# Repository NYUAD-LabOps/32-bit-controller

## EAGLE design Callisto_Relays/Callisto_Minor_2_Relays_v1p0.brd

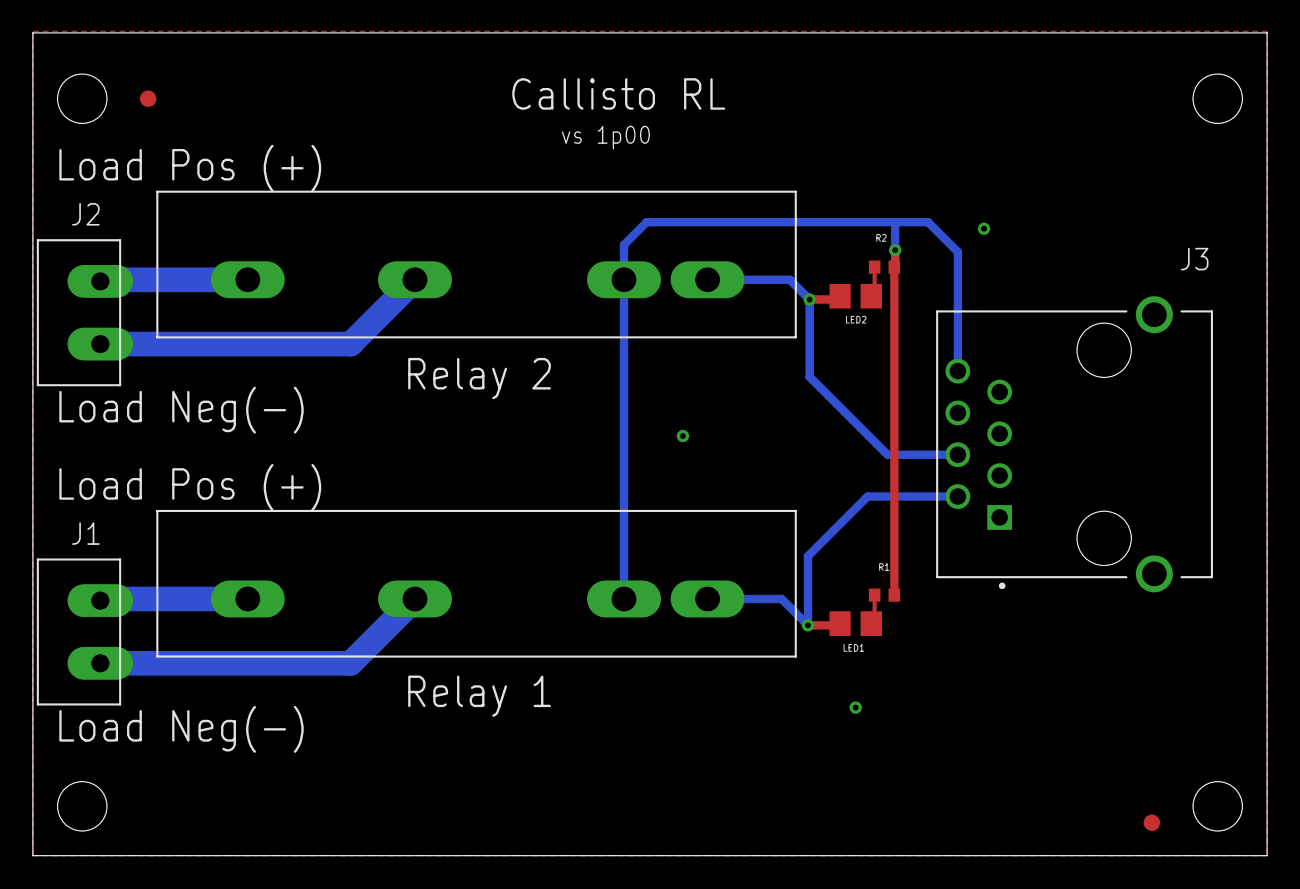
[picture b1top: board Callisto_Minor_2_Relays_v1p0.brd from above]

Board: 2 copper layers, 75.0 x 50.0 mm, 11 parts (0 on the bottom side), 10 nets.

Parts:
J1, J2: 2-pos; 2_3.81MM_PITCH
J3: RJ45_TH_VERT; ASSMANN_A-2014-2S-4-N-R
LED1, LED2: Green; 0805
R1, R2: 470R0; 0402
U$1, U$2: FIDUCIAL_1MM
U$3, U$5: RELAY_KYOTO_KF0604D

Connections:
GND: J3.1, J3.6
unnamed: LED1.1, R1.P$1
unnamed: LED2.1, R2.P$1
RELAY_1: J3.2, LED1.2, U$3.P$1
RELAY_2: J3.4, LED2.2, U$5.P$1
RO_NEG_1: J1.P$2, U$3.P$3
RO_NEG_2: J2.P$2, U$5.P$3
RO_POS_1: J1.P$1, U$3.P$4
RO_POS_2: J2.P$1, U$5.P$4
VDD5: J3.8, R1.P$2, R2.P$2, U$3.P$2, U$5.P$2

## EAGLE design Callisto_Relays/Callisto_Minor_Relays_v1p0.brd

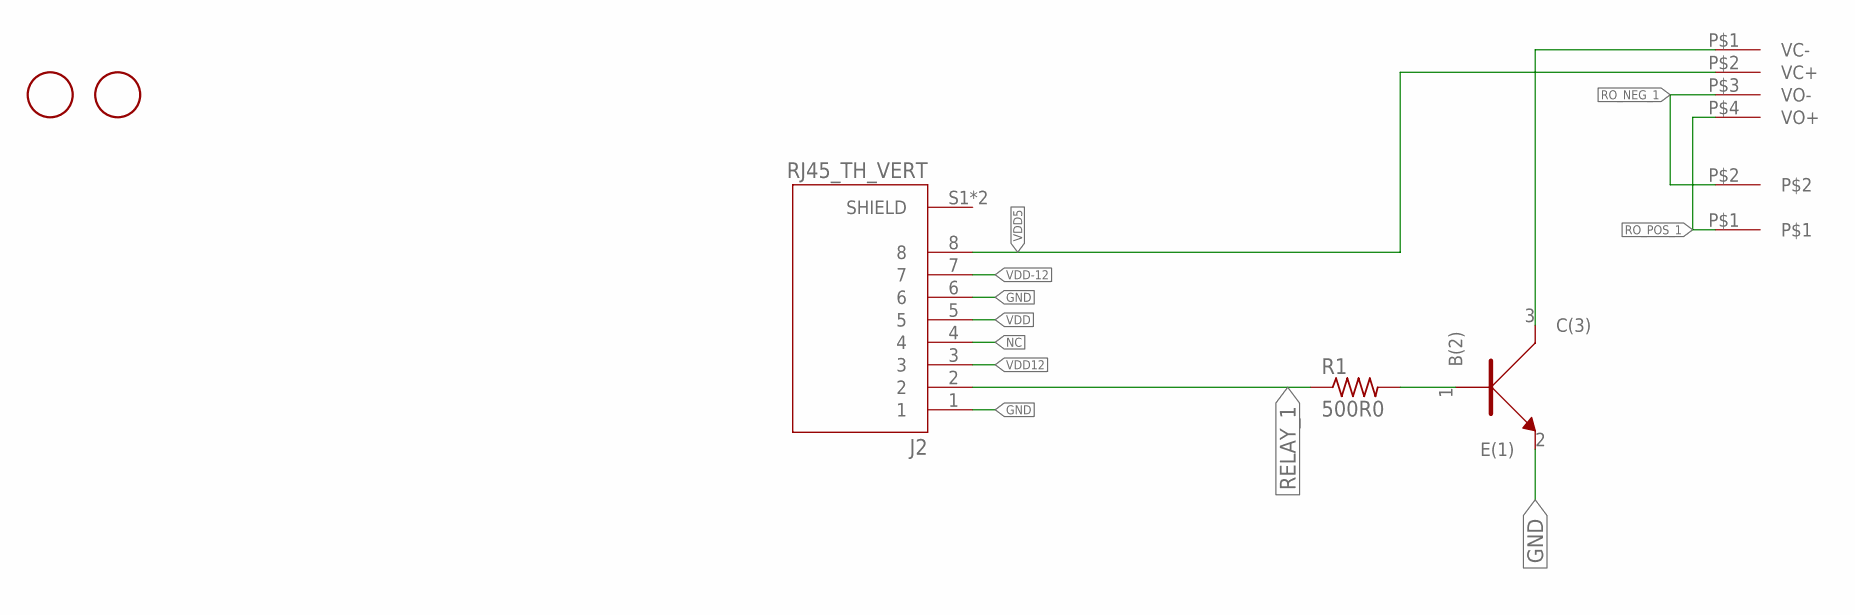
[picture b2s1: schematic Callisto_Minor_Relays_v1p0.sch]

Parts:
J1: 2-pos; 2_3.81MM_PITCH
J2: RJ45_TH_VERT; ASSMANN_A-2014-2S-4-N-R
R1: 500R0; 0402
U2: NPN; SOT323
U$1, U$2: FIDUCIAL_1MM
U$3: RELAY_KYOTO_KF0604D

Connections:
GND: J2.1, J2.6, U2.2 (E(1))
unnamed: R1.P$2 (2), U2.1 (B(2))
unnamed: U2.3 (C(3)), U$3.P$1 (VC-)
NC: J2.4
RELAY_1: J2.2, R1.P$1 (1)
RO_NEG_1: J1.P$2, U$3.P$3 (VO-)
RO_POS_1: J1.P$1, U$3.P$4 (VO+)
VDD: J2.5
VDD5: J2.8, U$3.P$2 (VC+)
VDD12: J2.3
VDD-12: J2.7

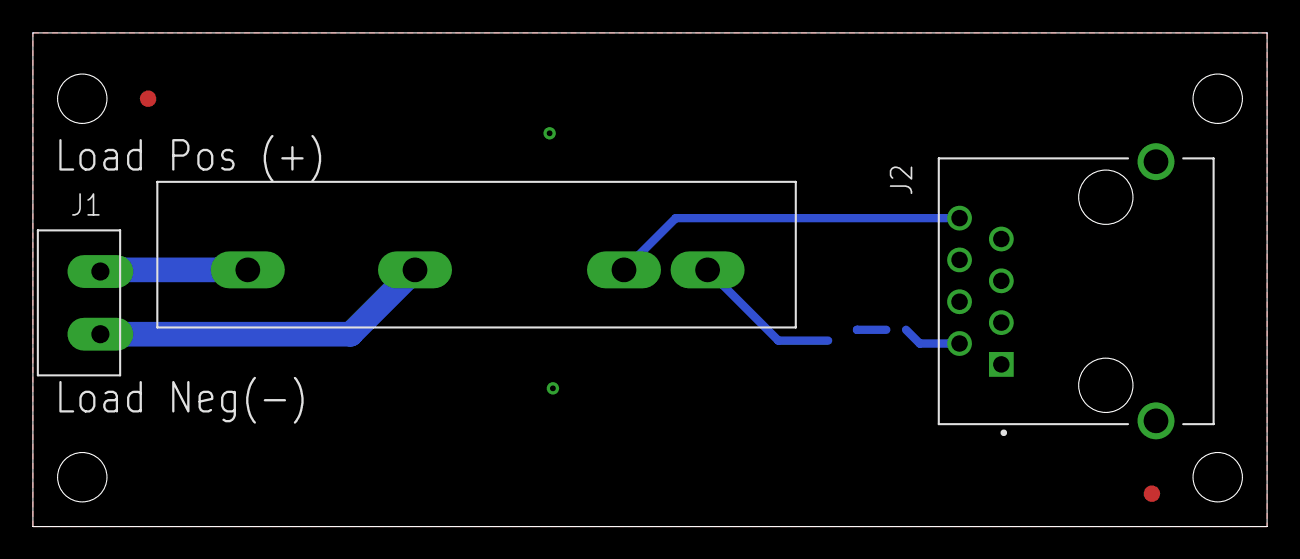
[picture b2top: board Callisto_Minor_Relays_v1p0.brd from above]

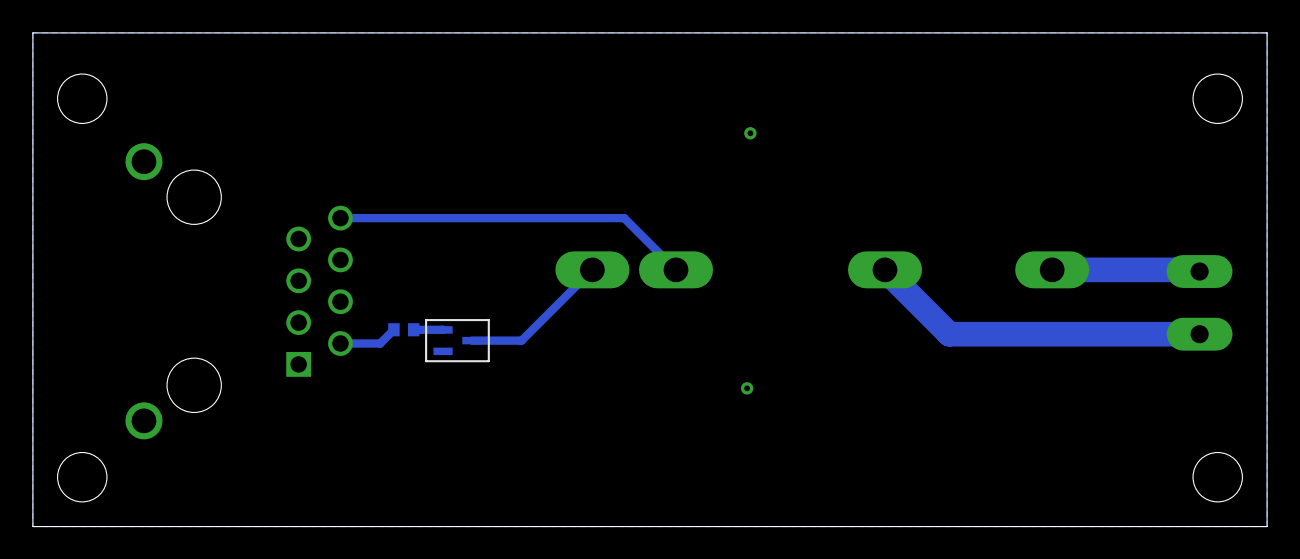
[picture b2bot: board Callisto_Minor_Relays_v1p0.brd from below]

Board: 2 copper layers, 75.0 x 30.0 mm, 7 parts (2 on the bottom side), 7 nets.

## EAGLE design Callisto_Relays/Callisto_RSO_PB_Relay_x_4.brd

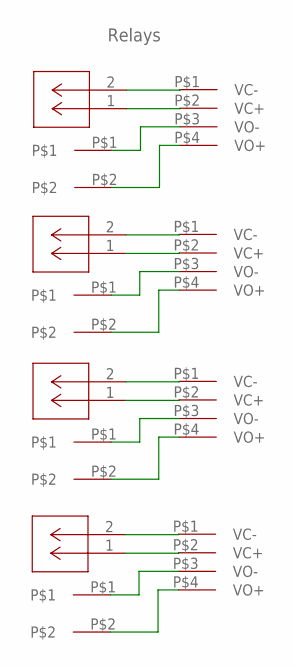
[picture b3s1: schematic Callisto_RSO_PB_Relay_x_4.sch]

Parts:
J4, J6, J8, J10: CONN_530470210_PICOBLADE_X_2; CON_530470210_MOL
J5, J7, J9, J11: 2-pos; 2_3.81MM_PITCH
U$1, U$2, U$3, U$4: RELAY_KYOTO_KF0604D

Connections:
unnamed: J4.1, U$1.P$2 (VC+)
unnamed: J4.2, U$1.P$1 (VC-)
unnamed: J5.P$1, U$1.P$3 (VO-)
unnamed: J5.P$2, U$1.P$4 (VO+)
unnamed: J6.1, U$2.P$2 (VC+)
unnamed: J6.2, U$2.P$1 (VC-)
unnamed: J7.P$1, U$2.P$3 (VO-)
unnamed: J7.P$2, U$2.P$4 (VO+)
unnamed: J8.1, U$3.P$2 (VC+)
unnamed: J8.2, U$3.P$1 (VC-)
unnamed: J9.P$1, U$3.P$3 (VO-)
unnamed: J9.P$2, U$3.P$4 (VO+)
unnamed: J10.1, U$4.P$2 (VC+)
unnamed: J10.2, U$4.P$1 (VC-)
unnamed: J11.P$1, U$4.P$3 (VO-)
unnamed: J11.P$2, U$4.P$4 (VO+)

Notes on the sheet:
Relays

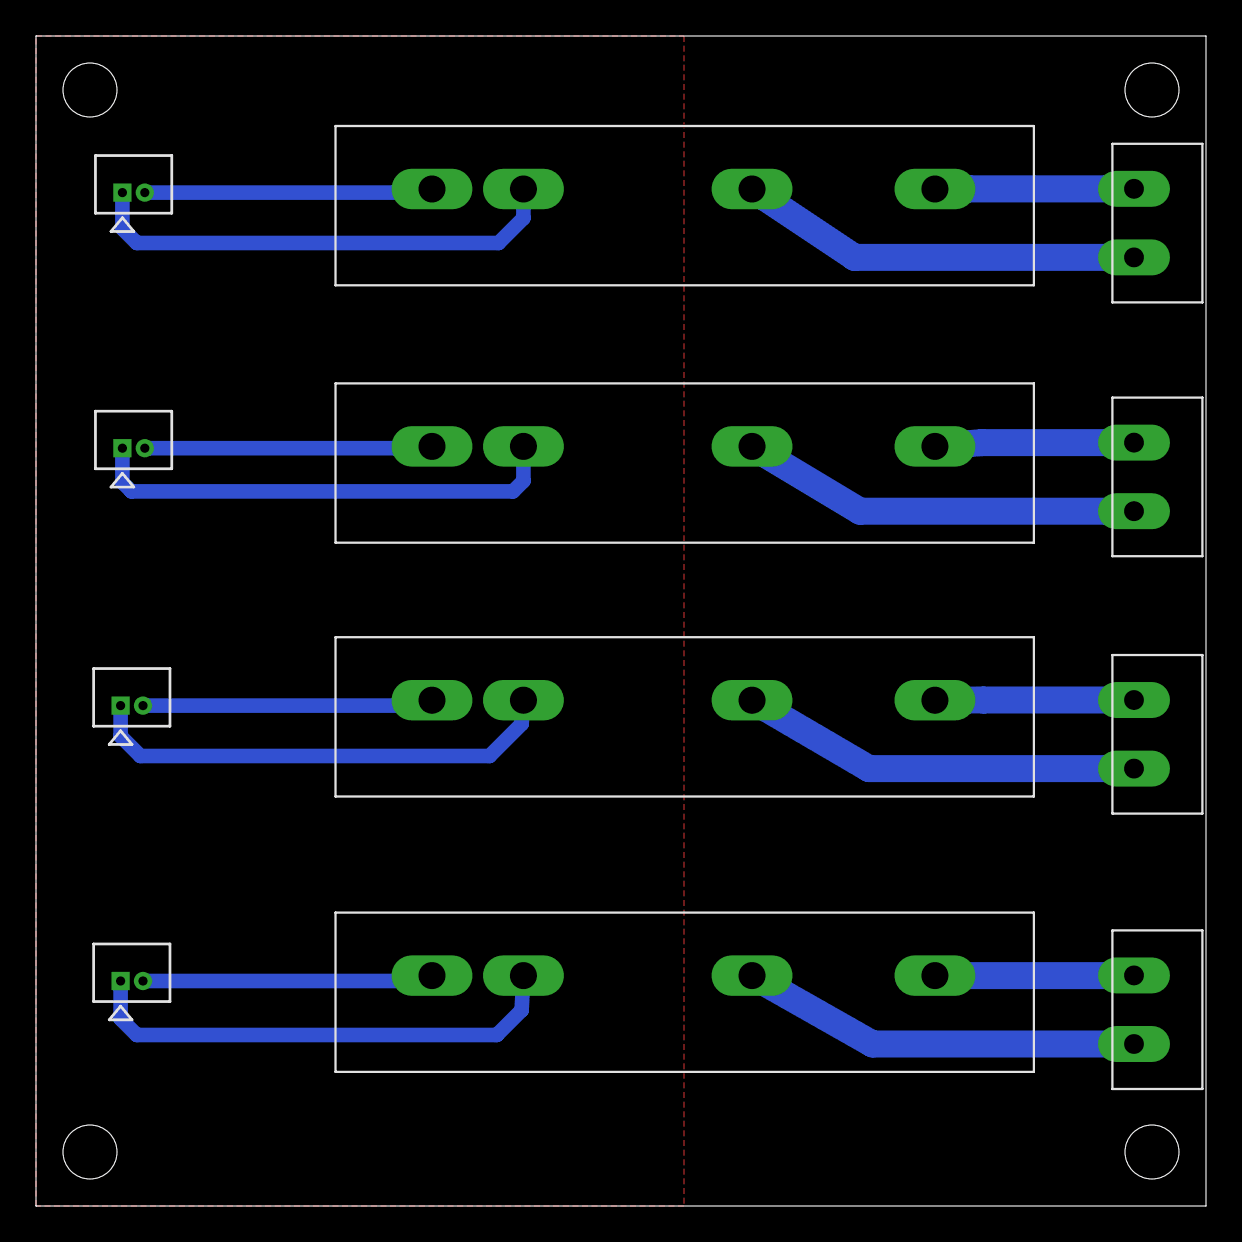
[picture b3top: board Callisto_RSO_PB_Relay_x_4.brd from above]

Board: 2 copper layers, 65.0 x 65.0 mm, 12 parts (0 on the bottom side), 16 nets.

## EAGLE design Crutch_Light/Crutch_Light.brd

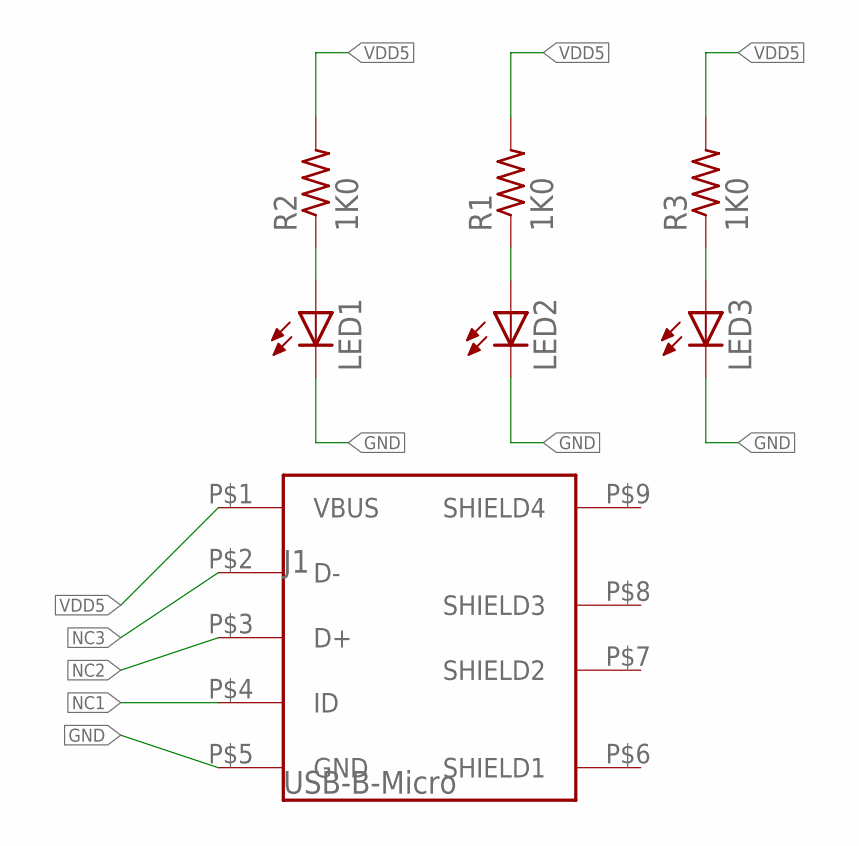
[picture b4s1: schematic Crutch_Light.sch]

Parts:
J1: USB-B-Micro; USB_MICRO-B
LED1, LED2, LED3: Green; 0805
R1, R2, R3: 1K0; 0402

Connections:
GND: J1.P$5 (GND), LED1.2 (C), LED2.2 (C), LED3.2 (C)
unnamed: LED1.1 (A), R2.P$1 (1)
unnamed: LED2.1 (A), R1.P$1 (1)
unnamed: LED3.1 (A), R3.P$1 (1)
NC1: J1.P$4 (ID)
NC2: J1.P$3 (D+)
NC3: J1.P$2 (D-)
VDD5: J1.P$1 (VBUS), R1.P$2 (2), R2.P$2 (2), R3.P$2 (2)

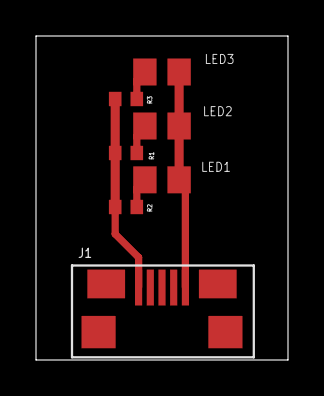
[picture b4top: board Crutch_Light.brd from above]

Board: 2 copper layers, 14.0 x 18.0 mm, 7 parts (0 on the bottom side), 5 nets.

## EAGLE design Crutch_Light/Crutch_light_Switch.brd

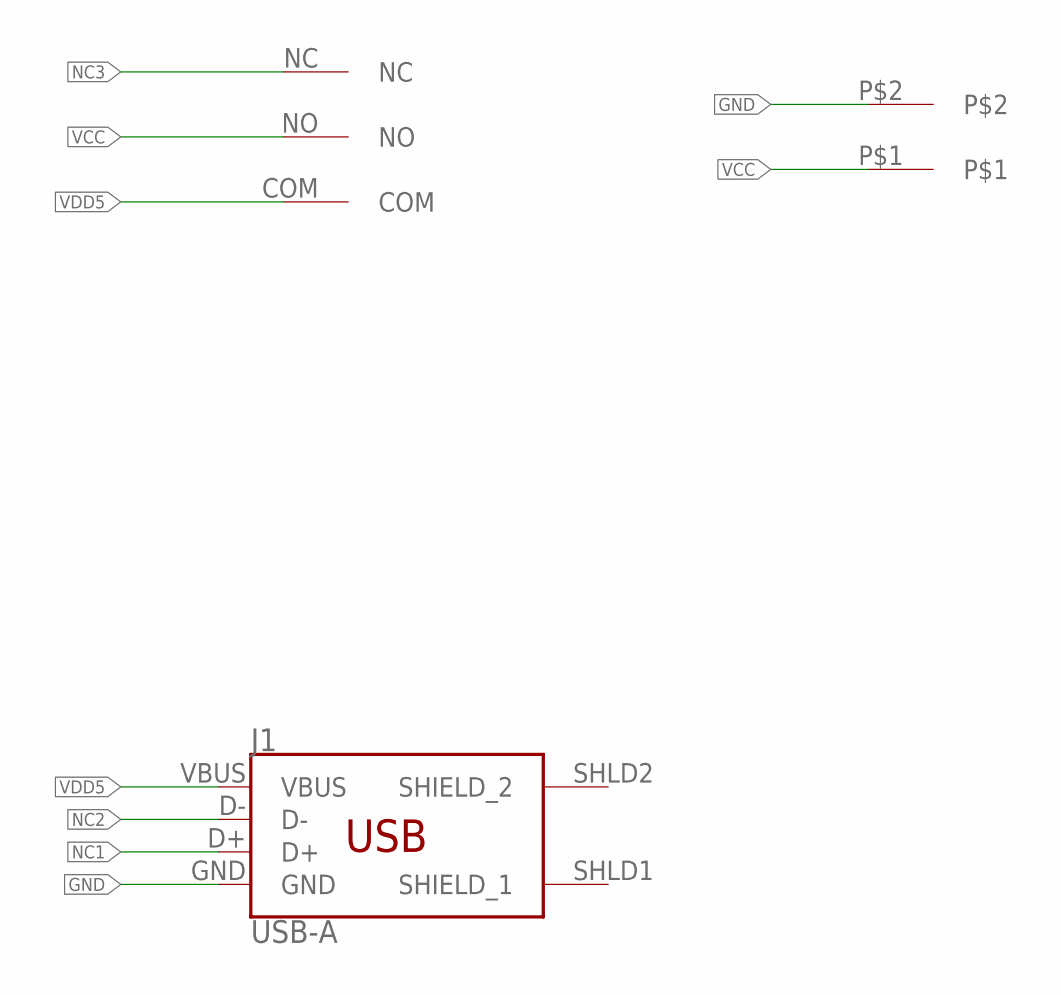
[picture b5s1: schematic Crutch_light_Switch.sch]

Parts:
J1: USB-A; USB_A_SMT
J2: 2-pos; 2_3.81MM_PITCH
U$1: LIMIT_SWITCH_D2HW-BR201DR

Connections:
GND: J1.GND, J2.P$2
NC1: J1.D+
NC2: J1.D-
NC3: U$1.NC
VCC: J2.P$1, U$1.NO
VDD5: J1.VBUS, U$1.COM

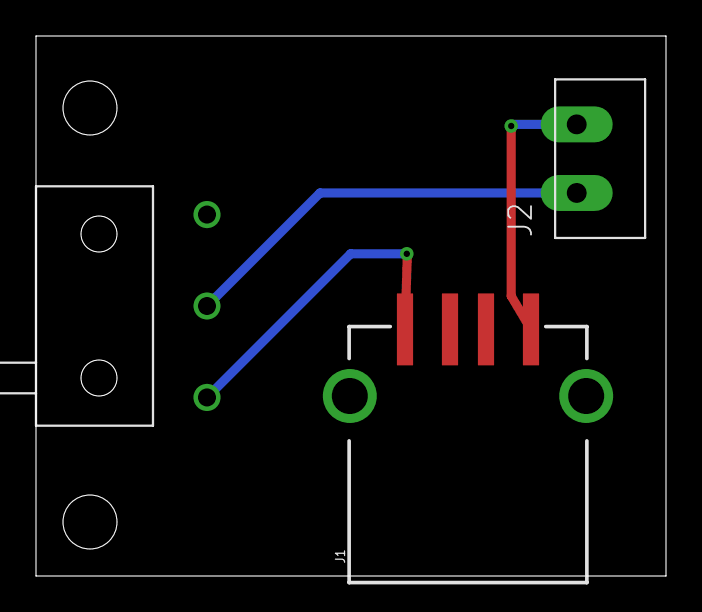
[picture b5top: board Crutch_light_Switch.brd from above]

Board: 2 copper layers, 35.0 x 30.0 mm, 3 parts (0 on the bottom side), 3 nets.

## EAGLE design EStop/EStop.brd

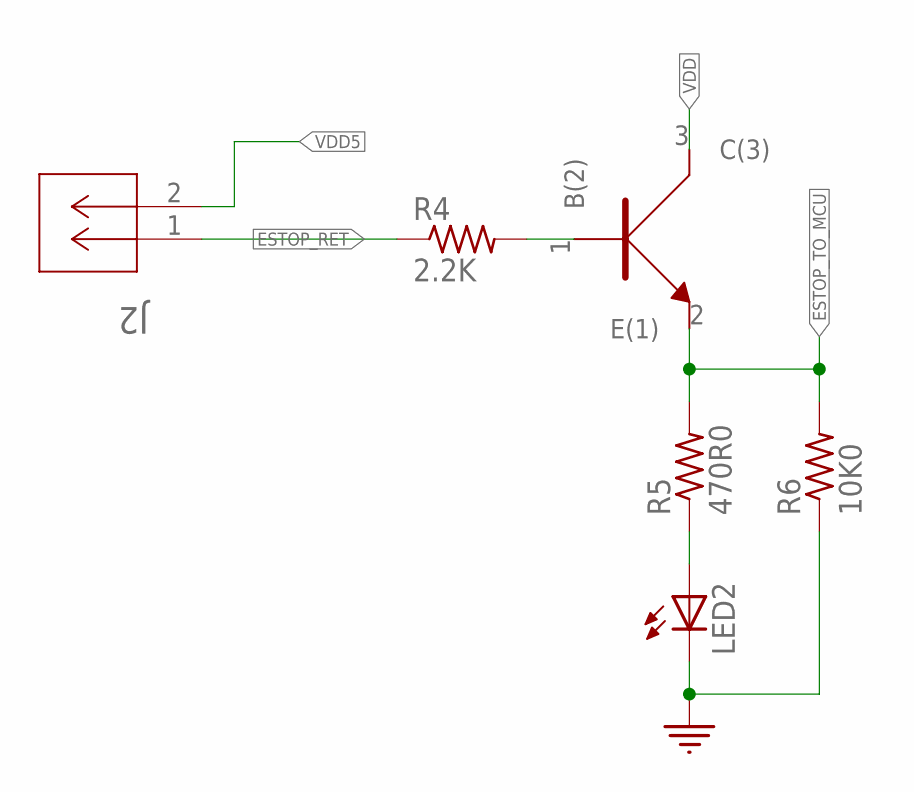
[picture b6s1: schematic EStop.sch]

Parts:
J2: CONN_530470210_PICOBLADE_X_2; CON_530470210_MOL
LED2: Green; 0805
R4: 2.2K; 0402
R5: 470R0; 0402
R6: 10K0; 0402
U2: NPN; SOT323

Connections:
ESTOP_RET: J2.1, R4.P$1 (1)
ESTOP_TO_MCU: R5.P$2 (2), R6.P$2 (2), U2.2 (E(1))
GND: LED2.2 (C), R6.P$1 (1)
unnamed: R4.P$2 (2), U2.1 (B(2))
unnamed: LED2.1 (A), R5.P$1 (1)
VDD: U2.3 (C(3))
VDD5: J2.2

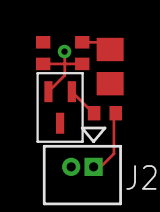
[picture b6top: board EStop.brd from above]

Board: 2 copper layers, 6 parts (0 on the bottom side), 5 nets.

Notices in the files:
parts and their libraries:
COPYRIGHT: Copyright (C) 2022 Ultra Librarian. All rights reserved.
